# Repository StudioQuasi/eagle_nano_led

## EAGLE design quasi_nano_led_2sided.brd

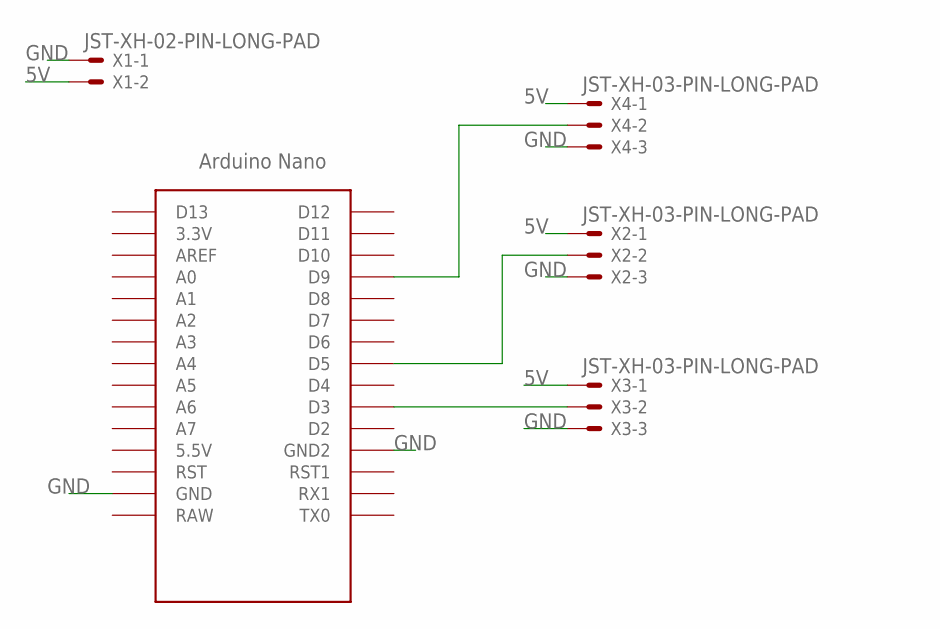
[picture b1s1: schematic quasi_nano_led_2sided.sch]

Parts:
U$1: NANO
X1: JST-XH-02-PIN-LONG-PAD; JST-XH-02-PACKAGE-LONG-PAD
X2, X3, X4: JST-XH-03-PIN-LONG-PAD; JST-XH-03-PACKAGE-LONG-PAD

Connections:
5V: X1.2, X2.1, X3.1, X4.1
GND: U$1.GND, U$1.GND1 (GND2), X1.1, X2.3, X3.3, X4.3
unnamed: U$1.D9, X4.2
unnamed: U$1.D5, X2.2
unnamed: U$1.D3, X3.2

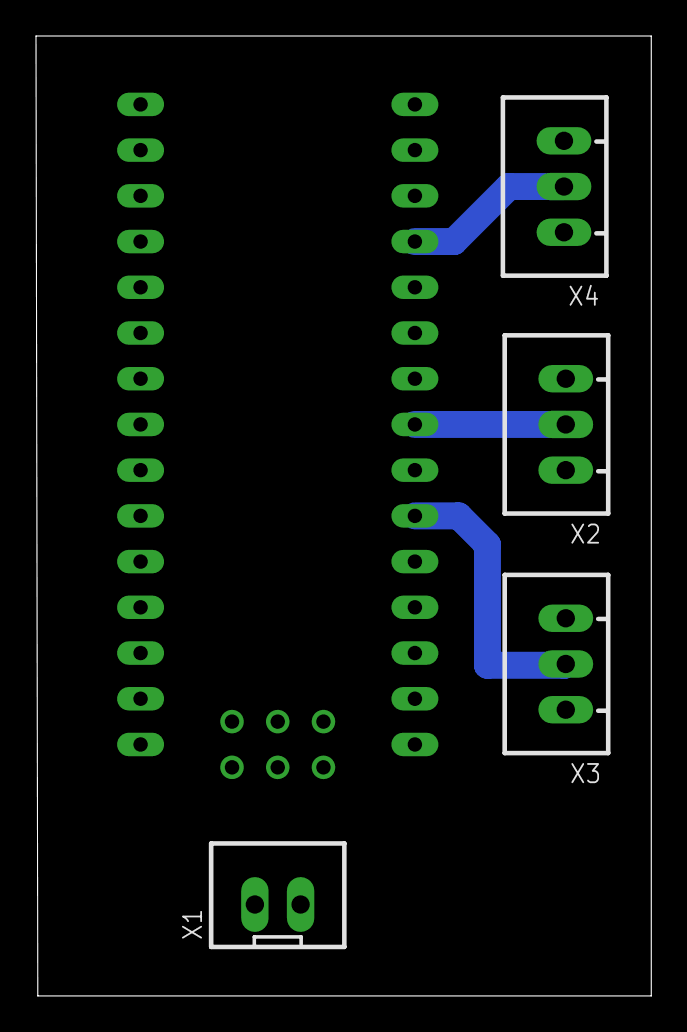
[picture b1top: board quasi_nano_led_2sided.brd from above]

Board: 2 copper layers, 34.2 x 53.3 mm, 5 parts (0 on the bottom side), 5 nets.

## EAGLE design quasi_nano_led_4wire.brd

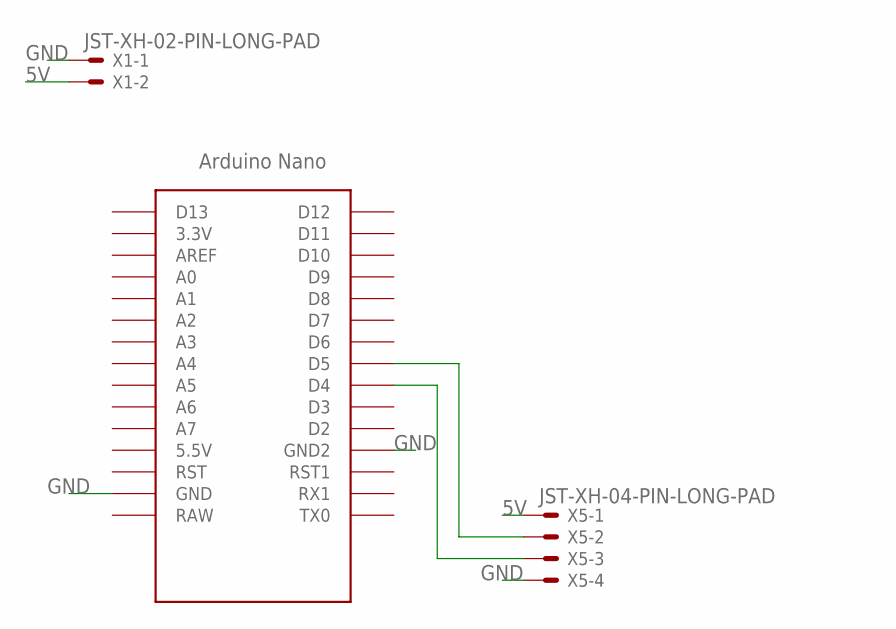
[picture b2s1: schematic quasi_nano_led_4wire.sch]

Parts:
U$1: NANO
X1: JST-XH-02-PIN-LONG-PAD; JST-XH-02-PACKAGE-LONG-PAD
X5: JST-XH-04-PIN-LONG-PAD; JST-XH-04-PACKAGE-LONG-PAD

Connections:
5V: X1.2, X5.1
GND: U$1.GND, U$1.GND1 (GND2), X1.1, X5.4
unnamed: U$1.D5, X5.2
unnamed: U$1.D4, X5.3

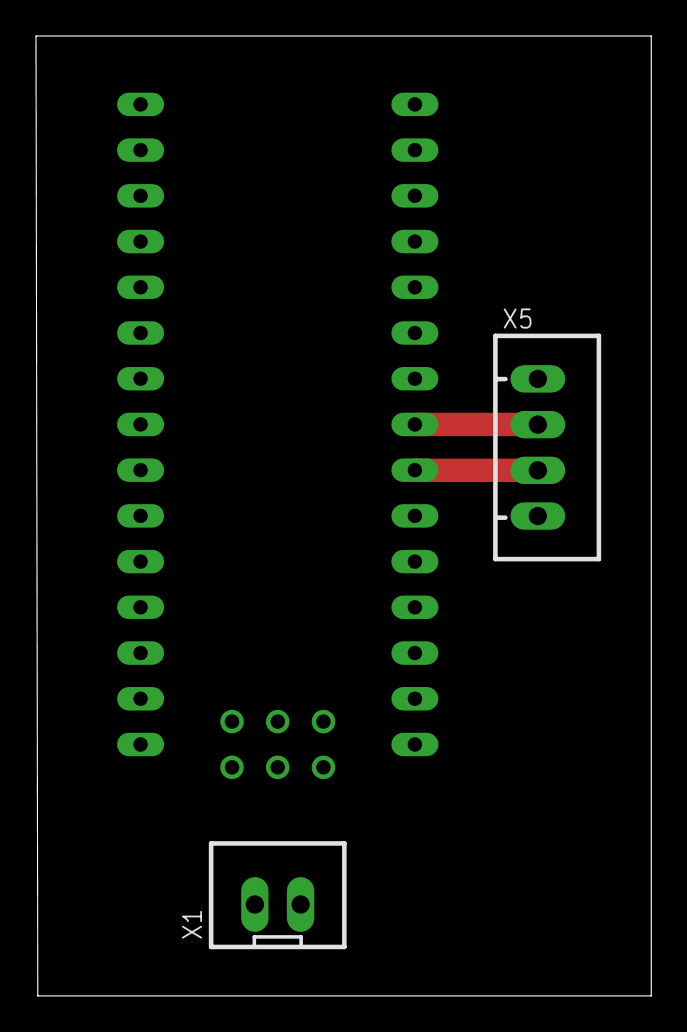
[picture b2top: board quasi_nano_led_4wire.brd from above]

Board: 2 copper layers, 34.2 x 53.3 mm, 3 parts (0 on the bottom side), 4 nets.

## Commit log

2019-08-05 first
2019-08-08 updated board
2020-11-06 add 4 wire board
